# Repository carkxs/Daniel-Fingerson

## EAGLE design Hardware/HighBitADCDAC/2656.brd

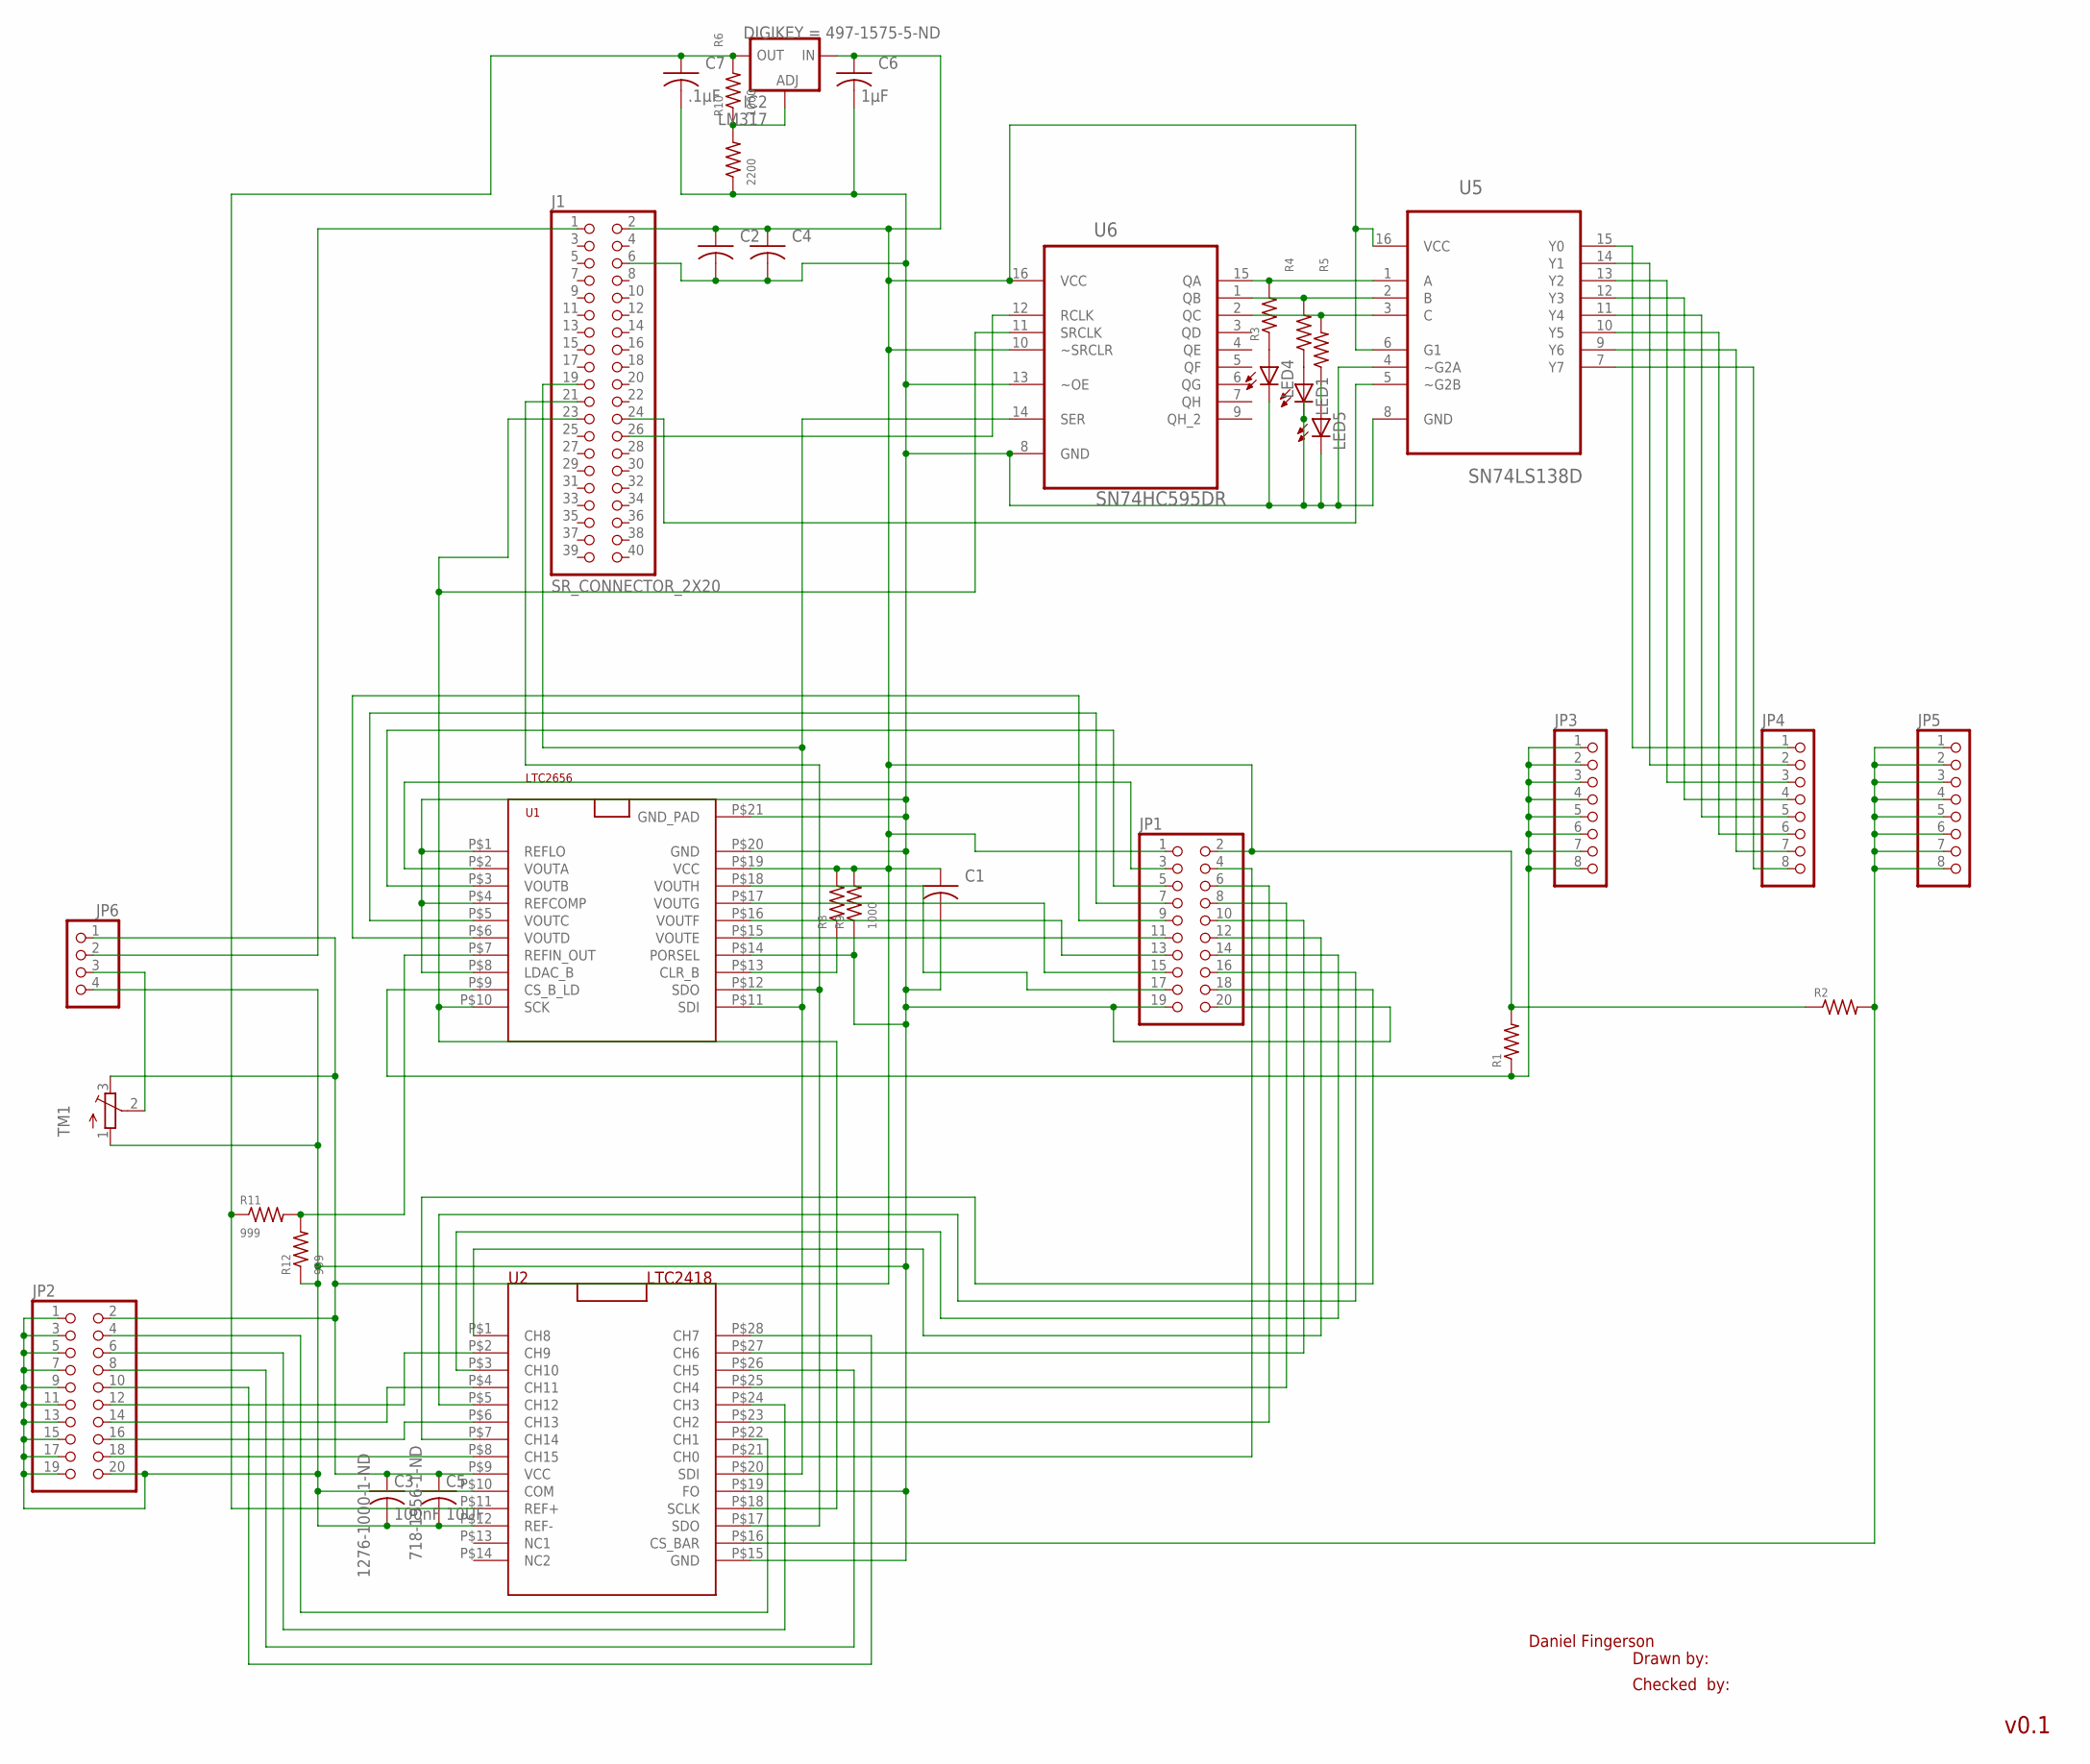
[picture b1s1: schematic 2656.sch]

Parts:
C1, C2, C4: C-USC1206; C1206
C3: 100nF; C1206; DIGIKEY 1276-1000-1-ND
C5: 10UF; C1206; DIGIKEY 718-1956-1-ND
C6: 1μF; C1206
C7: .1μF; C1206
IC2: LM317; 317TL; DIGIKEY 497-1575-5-ND
J1: SR_CONNECTOR_2X20
JP1, JP2: PINHD-2X10; 2X10
JP3, JP4, JP5: PINHD-1X8BIG; 1X08-BIG
JP6: PINHD-1X4; 1X04
LED1, LED4, LED5: LEDCHIPLED_1206; CHIPLED_1206
R1, R2, R3, R4, R5, R8: R-US_R1206; R1206
R6, R9: 1000; R1206
R10: 2200; R1206
R11, R12: 999; R1206
TM1: TRIMPOT3386; TRIM-3386
U1: LTC2656; SR_TSSOP20
U2: LTC2418; SR_SSOP28
U5: SN74LS138D; SOIC127P600X175-16N
U6: SN74HC595DR; SOIC127P600X175-16N

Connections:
unnamed: JP1.10, U2.P$27 (CH6)
unnamed: JP4.1, U5.15 (Y0)
unnamed: JP1.3, U1.P$2 (VOUTA)
unnamed: JP1.5, U1.P$3 (VOUTB)
unnamed: J1.23, U1.P$10 (SCK), U2.P$18 (SCLK), U6.11 (SRCLK)
unnamed: LED1.A, R4.1
unnamed: J1.21, U1.P$12 (SDO), U2.P$17 (SDO)
unnamed: J1.19, U1.P$11 (SDI), U2.P$20 (SDI), U6.14 (SER)
unnamed: R8.1, U1.P$13 (CLR_B)
unnamed: C1.2, C2.2, C3.2, C4.2, C5.2, C6.2, C7.2, J1.6, JP1.19, JP1.20, JP2.1, JP2.3, JP2.5, JP2.7, JP2.9, JP2.11, JP2.13, JP2.15, JP2.17, JP2.19, JP2.20, JP6.4, LED1.C, LED4.C, LED5.C, R9.1, R10.1, R12.1, TM1.1 (A), U1.P$1 (REFLO), U1.P$4 (REFCOMP), U1.P$8 (LDAC_B), U1.P$14 (PORSEL), U1.P$20 (GND), U1.P$21 (GND_PAD), U2.P$10 (COM), U2.P$12 (REF-), U2.P$15 (GND), U2.P$19 (FO), U5.4 (~G2A), U5.8 (GND), U6.8 (GND), U6.13 (~OE)
unnamed: JP1.7, U1.P$5 (VOUTC)
unnamed: JP1.4, U2.P$21 (CH0)
unnamed: R3.2, U5.1 (A), U6.15 (QA)
unnamed: JP1.9, U1.P$6 (VOUTD)
unnamed: JP1.11, U1.P$15 (VOUTE)
unnamed: JP1.13, U1.P$16 (VOUTF)
unnamed: R4.2, U5.2 (B), U6.1 (QB)
unnamed: R5.2, U5.3 (C), U6.2 (QC)
unnamed: JP1.15, U1.P$17 (VOUTG)
unnamed: JP1.17, U1.P$18 (VOUTH)
unnamed: JP1.6, U2.P$23 (CH2)
unnamed: J1.24, U5.5 (~G2B)
unnamed: JP1.8, U2.P$25 (CH4)
unnamed: JP1.18, U2.P$7 (CH14)
unnamed: J1.26, U6.12 (RCLK)
unnamed: JP4.2, U5.14 (Y1)
unnamed: JP1.12, U2.P$1 (CH8)
unnamed: JP1.14, U2.P$3 (CH10)
unnamed: JP1.16, U2.P$5 (CH12)
unnamed: JP2.4, U2.P$22 (CH1)
unnamed: JP2.6, U2.P$24 (CH3)
unnamed: JP2.8, U2.P$26 (CH5)
unnamed: JP2.10, U2.P$28 (CH7)
unnamed: JP2.18, U2.P$8 (CH15)
unnamed: JP4.3, U5.13 (Y2)
unnamed: JP2.12, U2.P$2 (CH9)
unnamed: JP2.14, U2.P$4 (CH11)
unnamed: JP2.16, U2.P$6 (CH13)
unnamed: JP4.4, U5.12 (Y3)
unnamed: JP4.5, U5.11 (Y4)
unnamed: JP4.6, U5.10 (Y5)
unnamed: JP4.7, U5.9 (Y6)
unnamed: JP4.8, U5.7 (Y7)
unnamed: JP3.1, JP3.2, JP3.3, JP3.4, JP3.5, JP3.6, JP3.7, JP3.8, R1.1, U1.P$9 (CS_B_LD)
unnamed: JP5.1, JP5.2, JP5.3, JP5.4, JP5.5, JP5.6, JP5.7, JP5.8, R2.2, U2.P$16 (CS_BAR)
unnamed: LED4.A, R3.1
unnamed: LED5.A, R5.1
unnamed: J1.1, JP6.2
unnamed: JP6.3, TM1.2 (S)
unnamed: C7.1, IC2.2 (OUT), R6.2, R11.1, U2.P$11 (REF+)
unnamed: IC2.1 (ADJ), R6.1, R10.2
V+3P3: R11.2, R12.2, U1.P$7 (REFIN_OUT)
V+5: C1.1, C2.1, C3.1, C4.1, C5.1, C6.1, IC2.3 (IN), J1.2, JP1.1, JP1.2, JP2.2, JP6.1, R1.2, R2.1, R8.2, R9.2, TM1.3 (E), U1.P$19 (VCC), U2.P$9 (VCC), U5.6 (G1), U5.16 (VCC), U6.10 (~SRCLR), U6.16 (VCC)

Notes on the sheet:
Drawn by:
Checked by:
Daniel Fingerson
v0.1

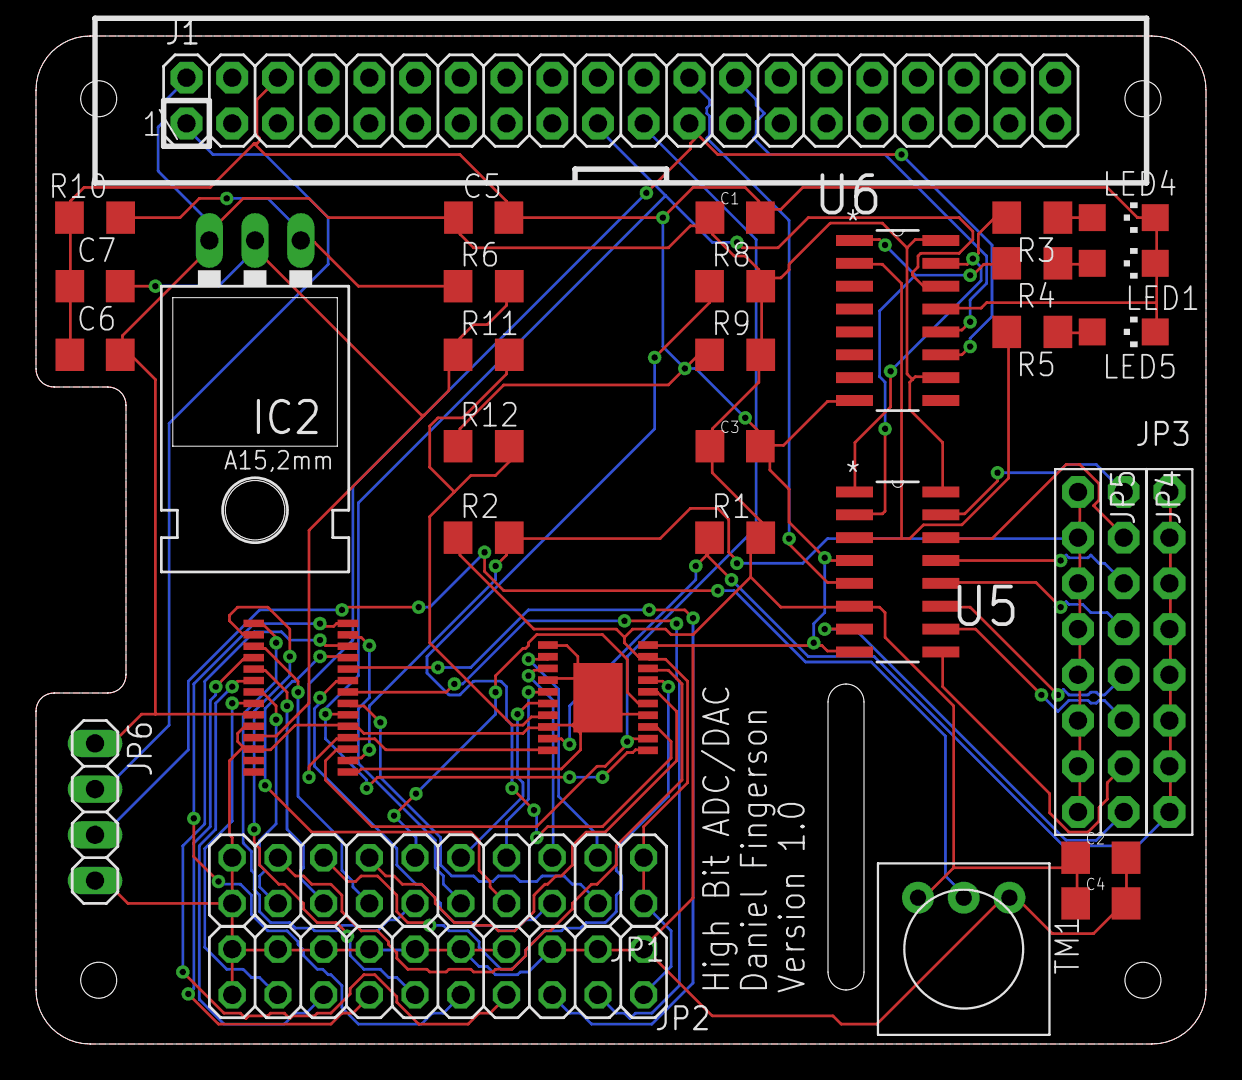
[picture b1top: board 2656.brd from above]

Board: 2 copper layers, 65.0 x 56.0 mm, 34 parts (0 on the bottom side), 53 nets.

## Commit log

2019-07-09 Create text
2019-07-24 Create a
2019-08-22 Update log.txt
    Month of July and half of august: delay due to broken computer
2019-12-18 Create HighBitADCDAC
